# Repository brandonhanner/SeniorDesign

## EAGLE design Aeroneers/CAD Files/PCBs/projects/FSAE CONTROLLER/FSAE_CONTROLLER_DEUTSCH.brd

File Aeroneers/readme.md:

## AeroCAN
![
](https://static1.squarespace.com/static/5c5a36a594d71ab0f5320f36/t/5cd09ff9104c7b2f4c380228/1557176321576/IMG_1575.jpg?format=2500w)
AeroCAN is all about removing the attention-load of the race car driver and enhancing a racers ability to get around track. It accomplishes this by reading in data from an onboard accelerometer, processing the signal with a digital signal processing algorithm, and controlling the action of control surfaces mounted on a motor vehicle.

## The System:

The system is logically split into three layers:

**The Data Acquisition Layer:**

This layer is responsible for reading the raw data from an IMU or Inertial Measurement Unit and applies a digital filter to the signal to reduce unwanted noise and anomalies.

**The Node Control Layer:**

This layer is responsible for receiving commands from the main control layer and enforcing those commands on physical control surfaces arranged around the car. It determines the position of the control surfaces by means of limit switches mounted on the car.

**The Main Control Layer:**

This layer is responsible for interpreting the data from the acquisition layer and orchestrating the control of the nodes in order to make the cars aero package, that is all control surfaces working together, function to the benefit of the driver.

# The Hardware:

From the outset, we chose to stick with components that were sufficient enough to do the job, but not excessively expensive such that the end result would never be a viable product.

With this in mind we chose the following components:

## **Node Board:**

-   Teensy 3.2 Arduino-compatible 32bit ARM Cortex M4 based microcontroller
    
-   Texas Instruments SN65HVD230 3.3V CAN Transceiver
    
-   Optically isolated digital inputs for control surface feedback
    
-   On board power regulation for protection against voltage fluctuations

## **Main Board:**

   Teensy 3.6 Arduino-compatible 32bit ARM Cortex M4 based microcontroller
    
-   Texas Instruments SN65HVD230 3.3V CAN Transceiver
    
-   Optically isolated digital inputs for human control feedback
    
-   On board power regulation for protection against voltage fluctuations
    
-   MPU9250 9-axis IMU

[Check out the PCB design files here](https://github.com/brandonhanner/SeniorDesign/tree/master/Aeroneers/CAD%20Files/PCBs/projects)

# The Software

**CAN Application Layer Protocol**

Rather than using the 11 bit CAN identifier to address each node individually, we decided a protocol is necessary to spread all of the functionality across the address space to facilitate ease of use and clarity of messages on the bus.

We achieved this by segmenting the 11 bit address space into two sections, the upper 5 bits of the address are reserved for “opcodes” so to speak, and the lower 6 bits are reserved for the address which an opcode is to act upon.

See the application protocol document for more reference: 

[AeroCAN Application Protocol](https://github.com/brandonhanner/SeniorDesign/blob/master/Aeroneers/Aeroneers%20CAN%20Protocol.pdf)

**AeroCAN Library**
The AeroCAN library was written to facilitate the implementation of an active aero system with different control theories. Our implementation is based solely off of the use of an accelerometer but by using the Teensy 3.6m you have access to a secondary CANbus which could open the door for using things like throttle, brake, steering angle, or any other operating parameters that might be available on a motorsports vehicle that could help teams perfect their control algorithm. This library lets users focus on control theory and leaves the operations of communication, control surface control, and configuration up to the library. 

While AeroCAN was developed on Teensy hardware and the FlexCAN library, it was designed such that the routines for CANcommunication could be adapted to specific hardware with relative ease. 

[Check out the library here](https://github.com/brandonhanner/SeniorDesign/tree/master/Aeroneers/libraries/AeroCAN)

# Demo Setup
Being a senior design project, we had to demo our project in the gym of the university. Since cars are not permitted in the gym, we decided to call in the help of Forza Motorsport 7's data out feature to send telemetry from the games physics engine to a wifi enabled microcontroller with a CAN peripheral to act as the main control board. Telemetry is sent via a 312 byte UDP packet containing over 70 parameters of telemetry, which is then parsed by the micro controller and the acceleration vectors are extracted and fed into the main layer to decide how the control surfaces should react. Attached via CANbus is three nodes controlling 3 servos with a aero control surface (model wing) attached to it. This is accomplished using the ForzaUDP2CANnoAeroCAN sketch on an ESP32 with the same CAN transceiver used in the final product.

[Check out the Demo Code here](https://github.com/brandonhanner/SeniorDesign/blob/master/Aeroneers/Sketches/ForzaUDP2CANnoAeroCAN/ForzaUDP2CANnoAeroCAN.ino)

[Demo Video of AeroCAN on YouTube](https://youtu.be/JjrttWb5x9Q)

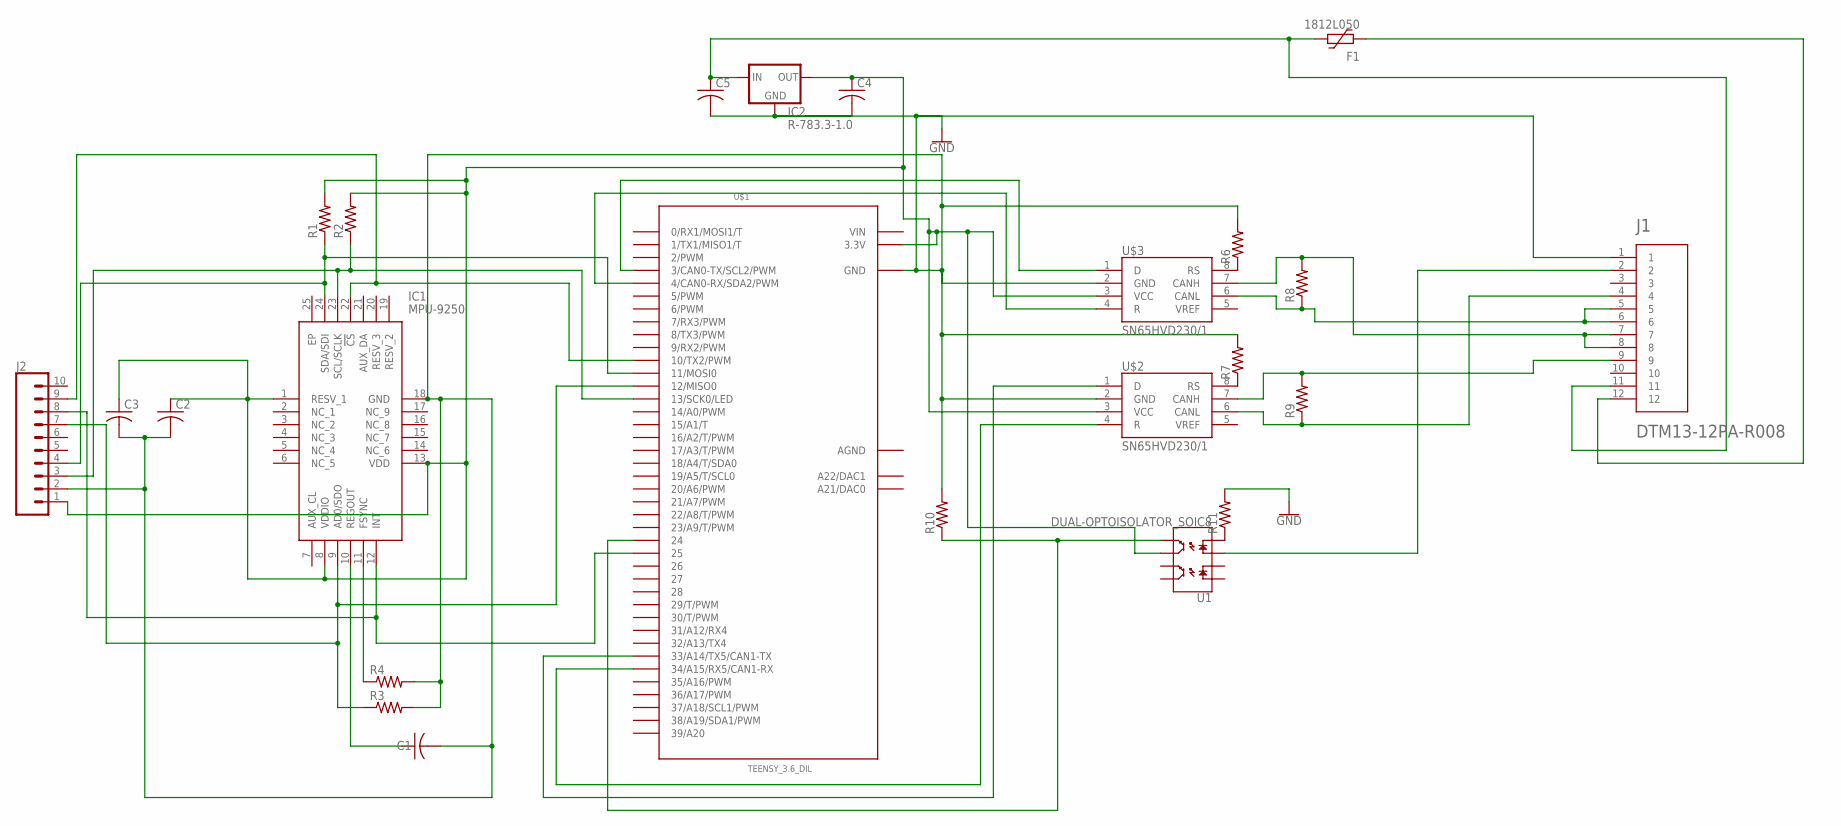
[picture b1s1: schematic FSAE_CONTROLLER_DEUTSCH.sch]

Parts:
C1, C2, C3, C4, C5: C-USC1206; C1206
F1: 1812L050; 1812L
IC1: MPU-9250; QFN40P300X300X105-25N
IC2: R-783.3-1.0; SIP3
J1: DTM13-12PA-R008; TE_DTM13-12PA-R008
J2: CONN_10"; 1X10
R1, R2, R3, R4, R6, R7, R8, R9, R10, R11: R-US_R1206; R1206
U1: DUAL-OPTOISOLATOR_SOIC8; SO08
U$1: TEENSY_3.6_DIL
U$2, U$3: SN65HVD230/1; SO8

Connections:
AGND: U$1.AGND
GND: C1.2, C2.2, C3.2, C4.2, C5.2, IC1.18 (GND), IC2.2 (GND), J1.1, J2.2, R3.2, R4.2, R6.2, R7.2, R10.2, R11.2, U$1.GND, U$1.GND1 (GND), U$2.2 (GND), U$3.2 (GND)
unnamed: C5.1, F1.1, IC2.1 (IN), J1.11
unnamed: IC1.11 (FSYNC), R4.1
unnamed: C1.1, IC1.10 (REGOUT)
unnamed: IC1.23 (SCL/SCLK), J2.3, R2.1, U$1.13 (13/SCK0/LED)
unnamed: IC1.24 (SDA/SDI), J2.4, R1.1, U$1.11 (11/MOSI0)
unnamed: IC1.9 (AD0/SDO), J2.7, R3.1, U$1.12 (12/MISO0)
unnamed: IC1.22 (!CS), J2.9, U$1.10 (10/TX2/PWM)
unnamed: R6.1, U$3.8 (RS)
unnamed: R7.1, U$2.8 (RS)
unnamed: U$1.3 (3/CAN0-TX/SCL2/PWM), U$3.1 (D)
unnamed: U$1.4 (4/CAN0-RX/SDA2/PWM), U$3.4 (R)
unnamed: J1.9, R9.2, U$2.7 (CANH)
unnamed: J1.7, J1.8, R8.2, U$3.7 (CANH)
unnamed: J1.5, J1.6, R8.1, U$3.6 (CANL)
unnamed: J1.4, R9.1, U$2.6 (CANL)
unnamed: U$1.33/A14 (33/A14/TX5/CAN1-TX), U$2.1 (D)
unnamed: U$1.34/A15 (34/A15/RX5/CAN1-RX), U$2.4 (R)
unnamed: F1.2, J1.12
unnamed: R10.1, U1.5 (EM2), U$1.24
unnamed: R11.1, U1.4 (C2)
unnamed: J1.2, U1.3 (A2)
unnamed: C2.1, C3.1, C4.1, IC1.1 (RESV_1), IC1.8 (VDDIO), IC1.13 (VDD), IC2.3 (OUT), J2.1, R1.2, R2.2, U1.6 (CL2), U$1.3.3V, U$1.3.3V3 (3.3V), U$2.3 (VCC), U$3.3 (VCC)
unnamed: IC1.12 (INT), J2.8, U$1.25
VIN: U$1.VIN

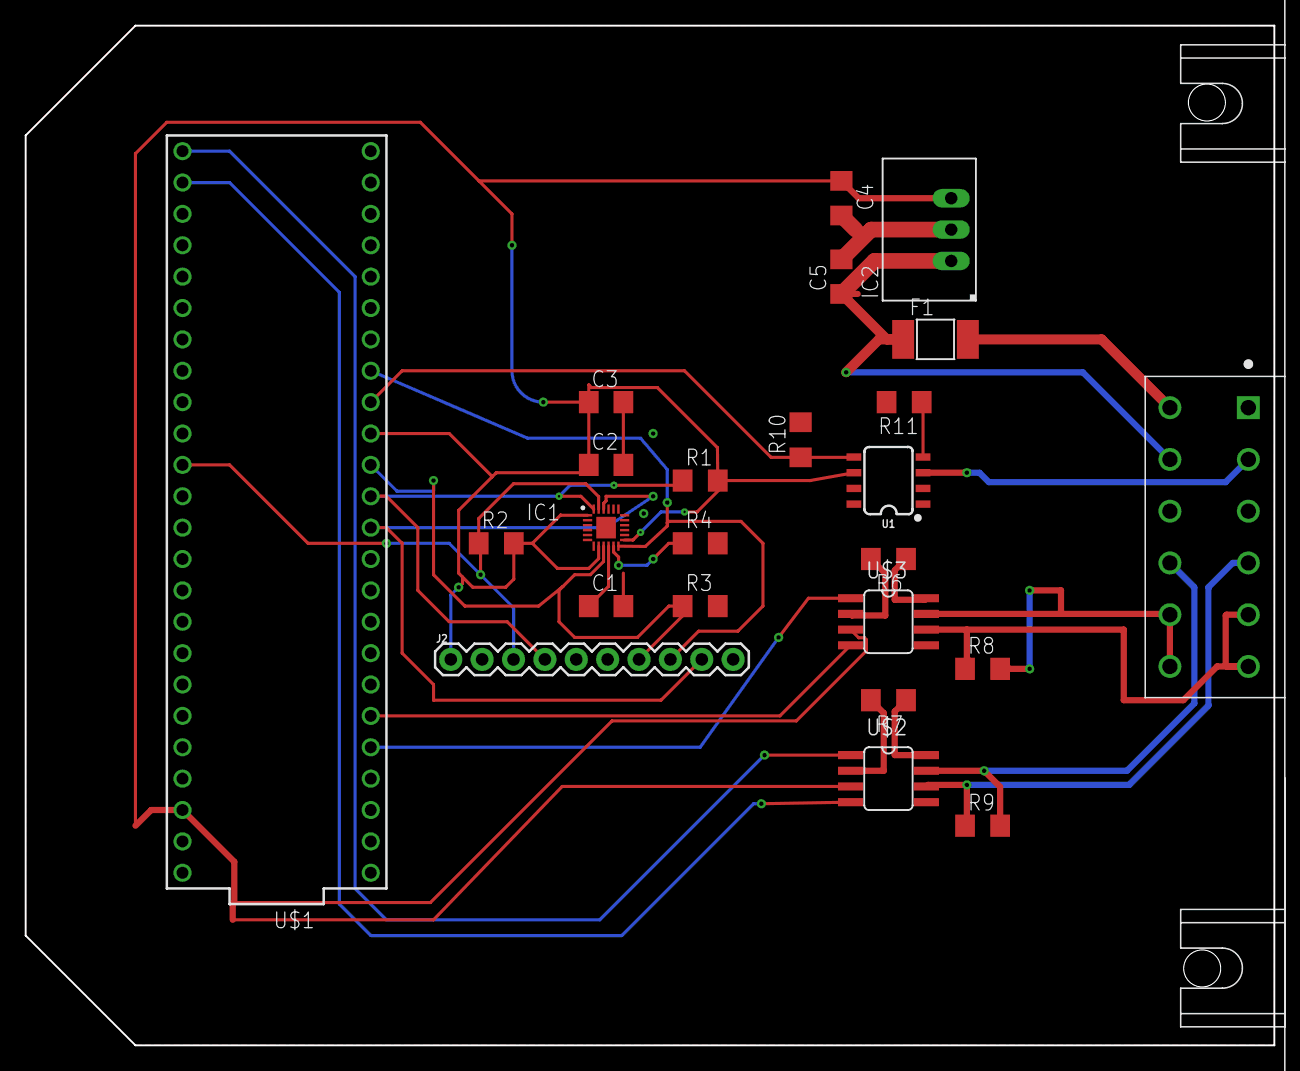
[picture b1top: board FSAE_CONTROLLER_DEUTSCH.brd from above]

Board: 2 copper layers, 101.1 x 82.5 mm, 24 parts (0 on the bottom side), 24 nets.

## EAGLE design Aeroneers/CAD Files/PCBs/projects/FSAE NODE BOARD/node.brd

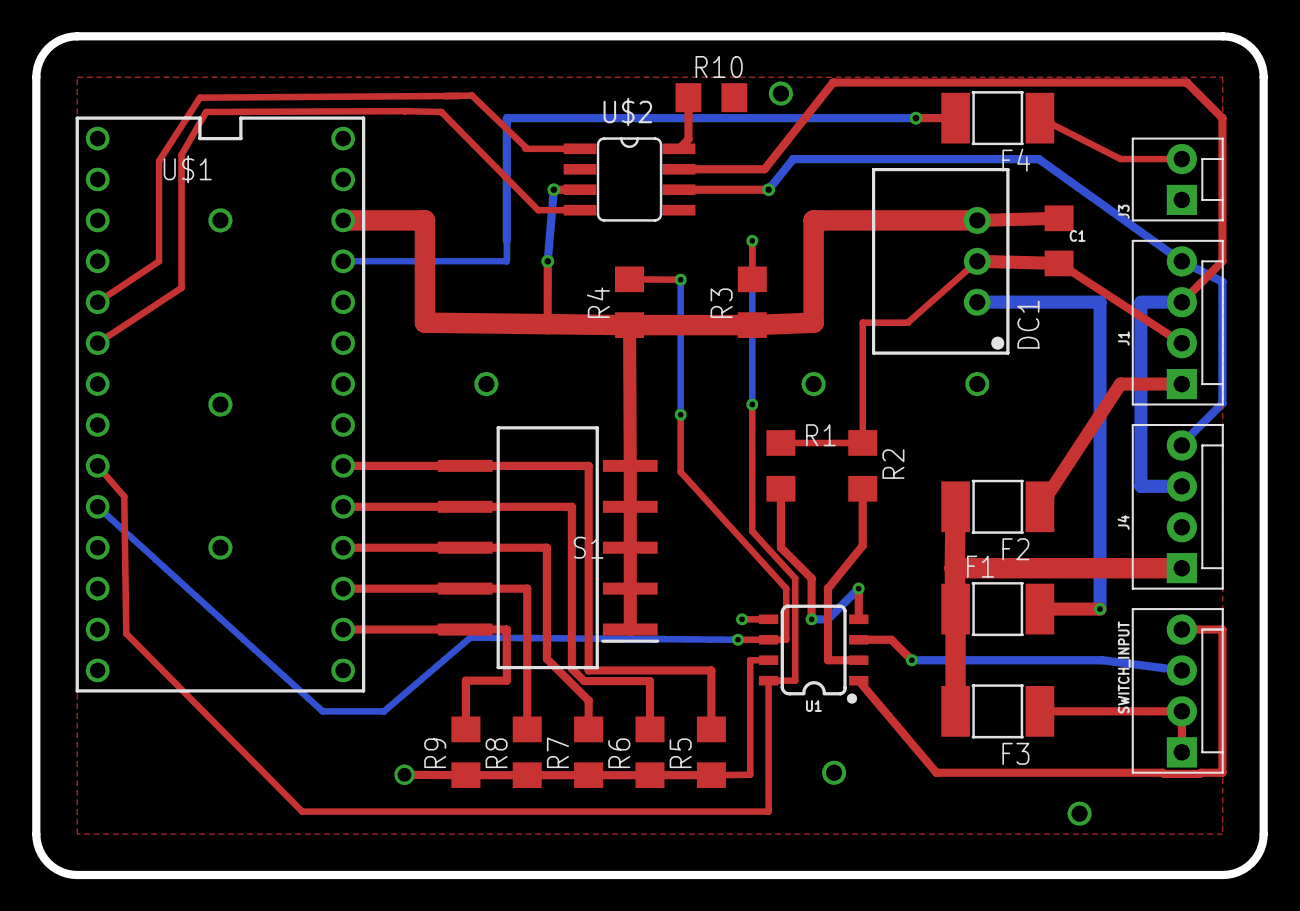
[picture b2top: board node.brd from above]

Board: 2 copper layers, 76.2 x 52.1 mm, 24 parts (0 on the bottom side), 24 nets.

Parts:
C1: 10uF; 1206
DC1: R-78C1.8-1.0; SIP3
F1, F3: 1812L050; 1812L
F2: 1812L110/16; 1812L
F4: 1812L010; 1812L
J1, J4: MOLEX-1X4
J3: MOLEX-1X2
R1, R2, R3, R4, R5, R6, R7, R8, R9, R10: R1206
S1: 204-5ST; SOP254P1152X760-10N
SWITCH_INPUT: MOLEX-1X4
U1: DUAL-OPTOISOLATOR_SOIC8; SO08
U$1: TEENSY_3.0_DIL; TEENSY_3.0-3.2&LC_DIL
U$2: SN65HVD230/1; SO8

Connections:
GND: C1.2, DC1.2, J1.2, J4.2, R1.1, R2.1, R5.1, R6.1, R7.1, R8.1, R9.1, R10.2, U1.5, U1.7, U$1.GND, U$2.2
unnamed: U$1.3, U$2.1
unnamed: U$1.4, U$2.4
unnamed: C1.1, DC1.3, R3.1, R4.1, S1.1, S1.2, S1.3, S1.4, S1.5, U$1.3.3V, U$2.3
unnamed: SWITCH_INPUT.3, U1.3
unnamed: SWITCH_INPUT.4, U1.1
unnamed: F4.1, J3.2
unnamed: J1.3, J4.3, U$2.7
unnamed: J1.4, J4.4, U$2.6
unnamed: R9.2, S1.10, U$1.14/A0
unnamed: R1.2, U1.4
unnamed: R2.2, U1.2
unnamed: R3.2, U1.8, U$1.7
unnamed: R4.2, U1.6, U$1.8
unnamed: F1.1, F2.2, F3.2, J4.1
unnamed: F2.1, J1.1
unnamed: F3.1, SWITCH_INPUT.1, SWITCH_INPUT.2
unnamed: R8.2, S1.9, U$1.15/A1
unnamed: R7.2, S1.8, U$1.16/A2
unnamed: R6.2, S1.7, U$1.17/A3
unnamed: R5.2, S1.6, U$1.18/A4
unnamed: F4.2, U$1.23/A9
unnamed: DC1.1, F1.2
unnamed: R10.1, U$2.8

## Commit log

2018-11-12 First Commit
    First Commit, with the driver for the MPU-9250 operational. Fleshing out the acquisition class, but only have the IMU class fully done, still working on filter and need to write the interface still.
2018-11-25 Test commit
2018-11-26 Testing some reatime stuff, no real updates here.. timertest was renamed timertest2 so I could restructure timertest to accomplish a different goal.
2018-12-03 Attempt at making faster reads from IMU
    added method on IMU class that doesnt pull temp or gyro readings in hopes that the read time drops..
2018-12-03 Updated timertest.cpp
    Updated to allow for mod of loop times and to add initial calibration of the sensor
2018-12-03 Messing with timertest
2018-12-03 updating timertest
    trying to figure out why loop can be less than 8ms in some cases..
2018-12-03 Cleaned up timertest
2019-02-21 First Commit since pivoting over to the new platform
2019-02-21 Sending TX test
2019-02-22 Added some examples for the team to test
2019-02-22 fixed blink to actually work
2019-02-22 temp upload before refactor
2019-02-22 refactored
2019-02-25 Removed RX & TX Test, consolidated into one program
2019-02-26 Organized the files for all the sketches, started on node firmware
2019-02-26 Added millis timers to make the timeout function actually work.
2019-02-26 Fully commented the node firmware, still not fully done though
2019-02-26 another update
2019-02-28 Node_Firmware approaching done state
    Node firmware is nearly done, Just need to implement the CAN protocol once it is decided and it will be ready to go. CAN is working with simple messages.
2019-03-18 Refactored folder to better organize everything. Added AeroCAN library
2019-03-18 updated CAN protocol to match google docs version
2019-03-18 Functioning filter that's timer based
2019-03-18 Filter and timer libraries
2019-03-18 deleting so I can add via folder
2019-03-18 working timer based filtering program
2019-03-19 DAQ implementation
2019-03-20 Updated DAQ
2019-03-21 Lots of updates
    Fixed AeroCAN library issues such that the AeroCAN firmware now does 90% of what its supposed to.. still a function left to implement to return config and status but it works otherwise.
    Updated Aero_Node_Tests file to send all message types to the node and it is correctly parsing those messages at this time.
    Added the Aero_Node_AeroCAN firmware, system is now in object oriented style.
2019-03-21 Added clean DAQ
2019-03-21 Updated AeroCAN
2019-03-21 Created main layer. Edited AeroCAN
2019-03-22 Added CAD Files for completed (minus connector) node board and schematic-complete main board
2019-04-08 OOP implementation
2019-05-07 End of semester commit
2019-05-07 created readme
2019-05-07 Removal of extraneous stuff
2019-05-08 got rid of icloud stuff

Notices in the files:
parts and their libraries:
r-78xx_10: (c) 2015 Samuel Lourenço
SparkFun-DiscreteSemi: Licensing: Creative Commons ShareAlike 4.0 International - https://creativecommons.org/licenses/by-sa/4.0
